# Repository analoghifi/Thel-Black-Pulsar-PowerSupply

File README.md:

# Thel "Black Pulsar" PowerSupply
Thel High-End "Class-A" Power Supply "Black Pulsar" (correctly: constant current parallel shunt voltage regulator)  

----
  
## Version 2013-2018:
https://web.archive.org/web/20160326152234/http://www.thel-audioworld.de/module/Class-A%20Netzteil/Blackpulsar.htm  
https://web.archive.org/web/20180819093402/http://www.thel-audioworld.de:80/module/Class-A%20Netzteil/Blackpulsar.htm  

.  
  
## Version 2019:
https://web.archive.org/web/20190630191455/http://thel-audioworld.de/module/Class-A%20Netzteil/Blackpulsar.htm  
  
### 10W:

### 25W:

----  
### Kicad projects in this repo:  
* [version 2013-2018](https://github.com/analoghifi/Thel-Black-Pulsar-PowerSupply/tree/main/hardware/version%202013-2018/KiCad/original) | state: initial release v1.01 | like the original, 1-layer, THT
*  [Black Pulsar 10W](https://github.com/analoghifi/Thel-Black-Pulsar-PowerSupply/tree/main/hardware/version%202019-now/10W/KiCad) (version 2019) | state: coming soon... | like the original, 1-layer, THT
*  [Black Pulsar 25W](https://github.com/analoghifi/Thel-Black-Pulsar-PowerSupply/tree/main/hardware/version%202019-now/25W/KiCad) (version 2019) | state: coming soon... | like the original, 1-layer, THT

----

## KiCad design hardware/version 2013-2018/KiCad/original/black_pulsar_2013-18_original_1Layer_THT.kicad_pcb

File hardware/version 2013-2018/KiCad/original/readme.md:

this is not the original Thel PCB but it's very like\* the original with the following exceptions:  
* more massive ground and power supply PCB tracks  
* using the 2mm gold-plated brass solder pins (the same ones used on the more expensive Thel modules)
* using a combined 5.0mm/7.5mm pin spacing footprint for the foil caps (C7,C14)  
* using a combined 2.5mm/5.0mm pin spacing footprint for the small ceramic caps (C4,C5,C11,C12)  
  
\*(same schematic / same 1-layer\** layout THT / same THT components in the same places on the board)  
\**(strictly speaking, this KiCad PCB is a two-layer PCB with plated-through holes, but you can also (let) produce it as a classic 1-layer PCB with non-plated holes if you wish, since all the tracks are on the bottom side only)  
  
----  
  
these are KiCad 6.x projects  
see how to get the proper 3D-Models from here: https://github.com/analoghifi/KiCad-3D-Models

use kicanvas.org to see this KiCad-Project in your browser:
https://kicanvas.org/?github=https%3A%2F%2Fgithub.com%2Fanaloghifi%2FThel-Black-Pulsar-PowerSupply%2Ftree%2Fmain%2Fhardware%2Fversion%25202013-2018%2FKiCad%2Foriginal

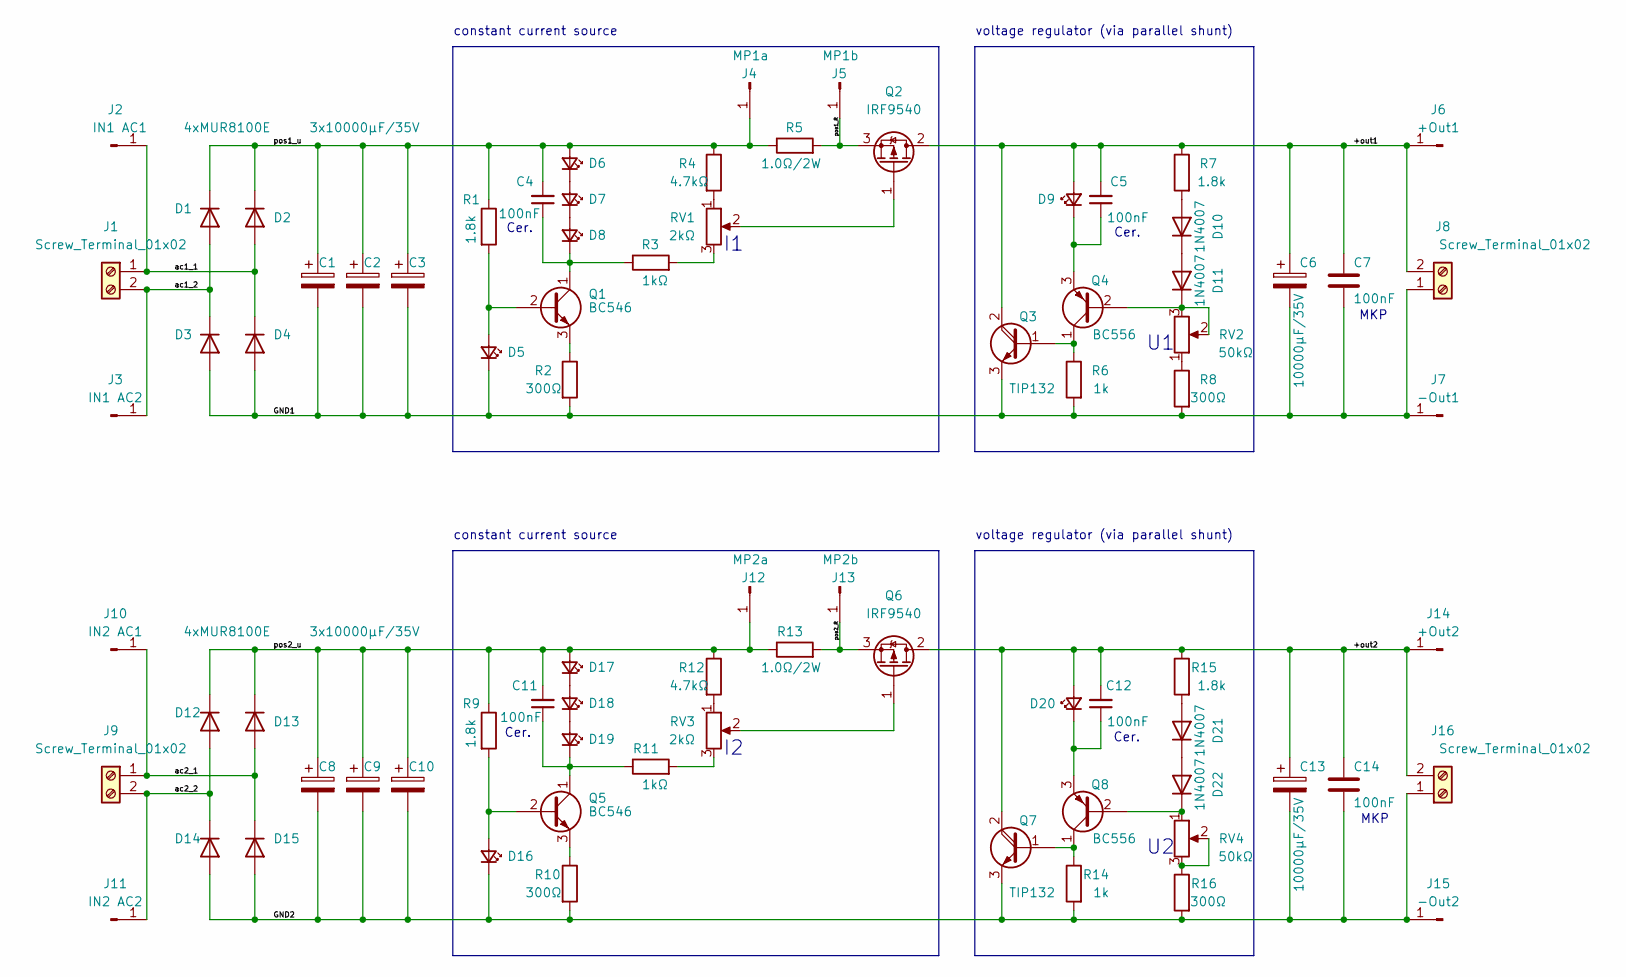
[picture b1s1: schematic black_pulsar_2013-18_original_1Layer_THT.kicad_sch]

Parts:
C1, C8: 3x10000µF/35V; CP_Radial_D22_H50_P10.00mm_SnapIn_min_silk
C2, C3, C9, C10: 2200µF; CP_Radial_D22_H50_P10.00mm_SnapIn_min_silk
C4, C5, C11, C12: 100nF; C_Rect_L7.0mm_W2.5mm_P2.50_5.00mm_min_silk
C6, C13: 10000µF/35V; CP_Radial_D22_H50_P10.00mm_SnapIn_min_silk
C7, C14: 100nF; C_Rect_L10.0mm_W4.0mm_P5.00_P7.50mm
D1, D12: 4xMUR8100E; TO-220-2_Vertical_noSilk
D2, D3, D4, D13, D14, D15: BYW29-200; TO-220-2_Vertical_noSilk
D5, D6, D7, D8, D9, D16, D17, D18, D19, D20: LED_Small; LED_D3.0mm
D10, D11, D21, D22: 1N4007; D_DO-41_SOD81_P10.16mm_Horizontal_minSilk
J1, J8, J9, J16: Screw_Terminal_01x02; TerminalBlock_Phoenix_PT-1,5-2-5.0-H_1x02_P5.00mm_Horizonta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
J2: IN1 AC1; Loet_Pin_D1.5mm_L14.0mm
J3: IN1 AC2; Loet_Pin_D1.5mm_L14.0mm
J4: MP1a; Loet_Pin_D1.5mm_L14.0mm
J5: MP1b; Loet_Pin_D1.5mm_L14.0mm
J6: +Out1; Loet_Pin_D1.5mm_L14.0mm
J7: -Out1; Loet_Pin_D1.5mm_L14.0mm
J10: IN2 AC1; Loet_Pin_D1.5mm_L14.0mm
J11: IN2 AC2; Loet_Pin_D1.5mm_L14.0mm
J12: MP2a; Loet_Pin_D1.5mm_L14.0mm
J13: MP2b; Loet_Pin_D1.5mm_L14.0mm
J14: +Out2; Loet_Pin_D1.5mm_L14.0mm
J15: -Out2; Loet_Pin_D1.5mm_L14.0mm
Q1, Q5: BC546; TO-92_wide
Q2, Q6: IRF9540; TO-220-3_Vertical
Q3, Q7: TIP132; TO-220-3_Vertical
Q4, Q8: BC556; TO-92_wide
R1, R7, R9, R15: 1.8k; R_Axial_DIN0207_L6.3mm_D2.5mm_P10.16mm_Horizontal_minSilk
R2, R10: 300Ω; R_Axial_DIN0207_L6.3mm_D2.5mm_P10.16mm_Horizontal_minSilk
R3, R11: 1kΩ; R_Axial_long_L6.3mm_D2.5mm_P11.43mm_Horizontal_minSilk
R4, R12: 4.7kΩ; R_Axial_long_L6.3mm_D2.5mm_P11.43mm_Horizontal_minSilk
R5, R13: 1.0Ω/2W; R_Axial_DIN0411_L9.9mm_D3.6mm_P12.70mm_Horizontal
R6, R14: 1k; R_Axial_DIN0207_L6.3mm_D2.5mm_P10.16mm_Horizontal_minSilk
R8, R16: 300Ω; R_Axial_long_L6.3mm_D2.5mm_P11.43mm_Horizontal_minSilk
RV1, RV3: 2kΩ; Potentiometer_Bourns_3386P_Vertical
RV2, RV4: 50kΩ; Potentiometer_Bourns_3296W_Vertical

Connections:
/+out1: C5.2, C6.1, C7.1, D9.2 (A), J6.1, J8.2, Q2.2 (D), Q3.2 (C), R7.1
/+out2: C12.2, C13.1, C14.1, D20.2 (A), J14.1, J16.2, Q6.2 (D), Q7.2 (C), R15.1
/GND1: C1.2, C2.2, C3.2, C6.2, C7.2, D3.2 (A), D4.2 (A), D5.1 (K), J7.1, J8.1, Q3.3 (E), R2.2, R6.2, R8.2
/GND2: C8.2, C9.2, C10.2, C13.2, C14.2, D14.2 (A), D15.2 (A), D16.1 (K), J15.1, J16.1, Q7.3 (E), R10.2, R14.2, R16.2
/ac1_1: D2.2 (A), D4.1 (K), J1.1, J2.1
/ac1_2: D1.2 (A), D3.1 (K), J1.2, J3.1
/ac2_1: D13.2 (A), D15.1 (K), J9.1, J10.1
/ac2_2: D12.2 (A), D14.1 (K), J9.2, J11.1
/pos1_R: J5.1, Q2.3 (S), R5.2
/pos1_u: C1.1, C2.1, C3.1, C4.2, D1.1 (K), D2.1 (K), D6.2 (A), J4.1, R1.1, R4.1, R5.1
/pos2_R: J13.1, Q6.3 (S), R13.2
/pos2_u: C8.1, C9.1, C10.1, C11.2, D12.1 (K), D13.1 (K), D17.2 (A), J12.1, R9.1, R12.1, R13.1
unnamed: C4.1, D8.1 (K), Q1.1 (C), R3.1
unnamed: C5.1, D9.1 (K), Q4.3 (E)
unnamed: C11.1, D19.1 (K), Q5.1 (C), R11.1
unnamed: C12.1, D20.1 (K), Q8.3 (E)
unnamed: D5.2 (A), Q1.2 (B), R1.2
unnamed: D6.1 (K), D7.2 (A)
unnamed: D7.1 (K), D8.2 (A)
unnamed: D10.1 (K), D11.2 (A)
unnamed: D10.2 (A), R7.2
unnamed: D11.1 (K), Q4.2 (B), RV2.2, RV2.3
unnamed: D16.2 (A), Q5.2 (B), R9.2
unnamed: D17.1 (K), D18.2 (A)
unnamed: D18.1 (K), D19.2 (A)
unnamed: D21.1 (K), D22.2 (A)
unnamed: D21.2 (A), R15.2
unnamed: D22.1 (K), Q8.2 (B), RV4.1
unnamed: Q1.3 (E), R2.1
unnamed: Q2.1 (G), RV1.2
unnamed: Q3.1 (B), Q4.1 (C), R6.1
unnamed: Q5.3 (E), R10.1
unnamed: Q6.1 (G), RV3.2
unnamed: Q7.1 (B), Q8.1 (C), R14.1
unnamed: R3.2, RV1.3
unnamed: R4.2, RV1.1
unnamed: R8.1, RV2.1
unnamed: R11.2, RV3.3
unnamed: R12.2, RV3.1
unnamed: R16.1, RV4.2, RV4.3

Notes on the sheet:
MKP
voltage regulator (via parallel shunt)
Cer.
constant current source

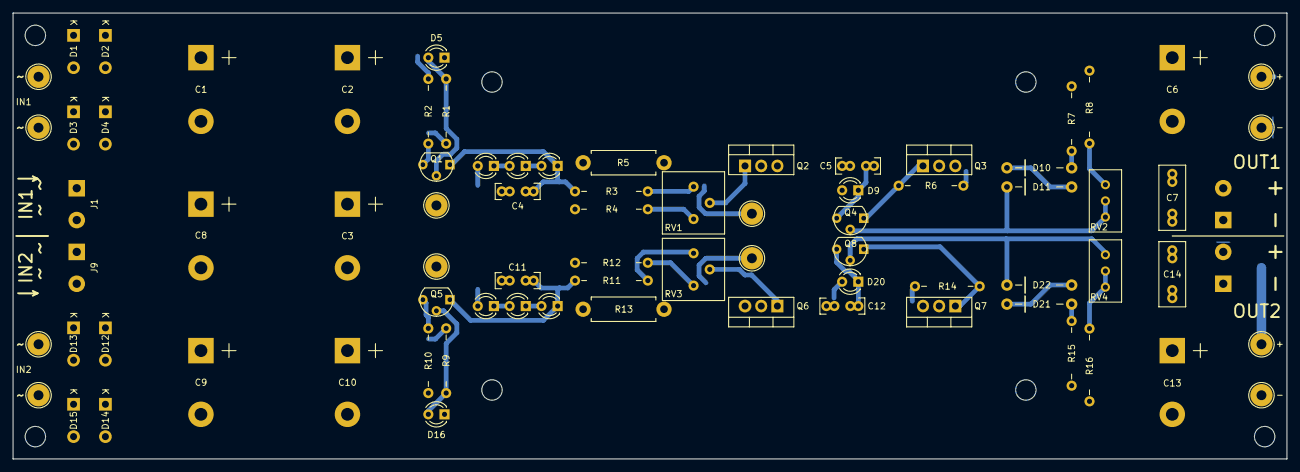
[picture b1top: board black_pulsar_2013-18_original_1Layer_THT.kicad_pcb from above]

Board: 2 copper layers, 200.0 x 70.0 mm, 80 parts (0 on the bottom side), 40 nets.
